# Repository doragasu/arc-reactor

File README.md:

# arc-reactor
Small PCB and 3D printed piece resembling one of Iron Man ARC reactor designs

# What's on this repo?
- sch directory: PCB design files (KiCAD, PDF and Gerber files).
- 3d directory: 3D printable piece (FreeCAD, SVG and STL files).
- src directory: Firmware for the ATtiny25/45/85 microcontroller, to make the LEDs slowly blink, as shown in the video: https://www.youtube.com/watch?v=LkEIsV0EnbI

# Author
All sources and CAD designs, made by doragasu.

# Status
This project is working perfect and considered finished.

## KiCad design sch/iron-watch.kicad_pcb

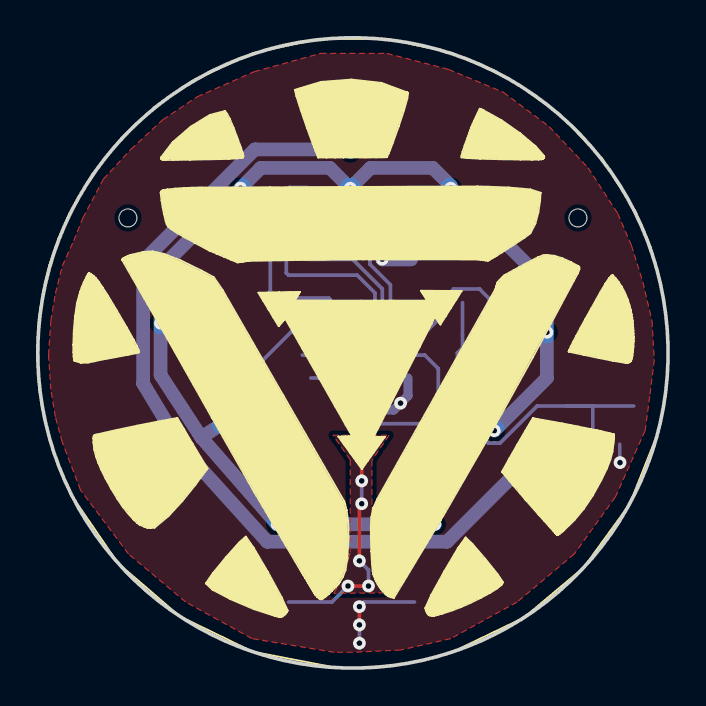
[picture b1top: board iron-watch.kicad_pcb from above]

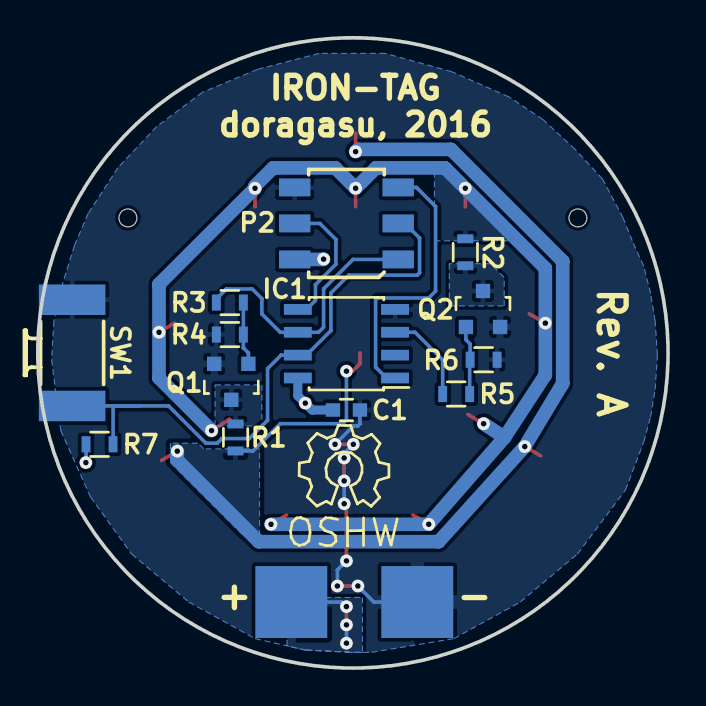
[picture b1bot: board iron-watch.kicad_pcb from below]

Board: 2 copper layers, 35.0 x 35.0 mm, 27 parts (14 on the bottom side), 13 nets.

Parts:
C1: 100n; C_0603
D1, D2, D3, D4, D5, D6, D7, D8, D9, D10, D11, D12, D13: LED; LED-0603
IC1: ATTINY85-S; SOIC-8_3.9x4.9mm_Pitch1.27mm
P1: CONN_01X02; CR2032L_F1N_PADS
P2: CONN_01X06; CON_3x2P_2MM_SMD
Q1, Q2: 2N7002; SOT-23
R1, R2: R; R_0603
R3, R5: 100; R_0603
R4, R6, R7: 47k; R_0603
SW1: SW_PUSH; C&K_KSS

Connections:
/LD1: D1.1, D2.1, D3.1, D4.1, R1.1
/LD2: D5.1, D6.1, D7.1, D8.1, D9.1, D10.1, D11.1, D12.1, D13.1, R2.1
GND: C1.2, IC1.4, P1.2, P2.6, Q1.2, Q2.2, R4.2, R6.2, SW1.2
unnamed: IC1.1, P2.5
unnamed: IC1.3, R5.1
unnamed: IC1.5, P2.4
unnamed: IC1.6, P2.1, R3.1
unnamed: IC1.7, P2.3, R7.2, SW1.1
unnamed: Q1.1, R3.2, R4.1
unnamed: Q1.3, R1.2
unnamed: Q2.1, R5.2, R6.1
unnamed: Q2.3, R2.2
VDD: C1.1, D1.2, D2.2, D3.2, D4.2, D5.2, D6.2, D7.2, D8.2, D9.2, D10.2, D11.2, D12.2, D13.2, IC1.8, P1.1, P2.2, R7.1

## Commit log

2016-07-30 Added design and source files.
